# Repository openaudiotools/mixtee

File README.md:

# MIXTEE

**Open-source 16-input / 8-output digital mixer with MIDI control and 16-track recording.**

Built around the Teensy 4.1, MIXTEE is a compact desktop mixer designed for electronic musicians, synth enthusiasts, and DIY audio builders. It handles mixing, monitoring, MIDI control, multitrack recording to SD card, and 16-in/8-out AES67 network audio — all in a 260 × 100 × 50 mm enclosure.

## Features

- **16 mono inputs** (8 stereo pairs) with per-channel gain, pan, mute, solo
- **8 outputs** (master stereo + 3 aux/FX sends)
- **16-track recording** direct to SD card (48 kHz / 24-bit WAV, 8 MB PSRAM buffer)
- **DAW connectivity** (16-in / 8-out via AES67 over Ethernet)
- **MIDI control** via 2× USB host ports + TRS MIDI in/out
- **4.3" TFT display** with 3 dedicated encoders (NavX, NavY, Edit) and 16 illuminated CHOC keys
- **Compact form factor** — 260 × 100 × 50 mm, all controls on top, all audio on back

## Architecture

MIXTEE uses four AK4619VN codecs on two TDM buses, driven by the Teensy 4.1's Cortex-M7 at 600 MHz. The analog front-end features OPA1678 op-amps with Sallen-Key anti-alias and reconstruction filters. Power is supplied via USB-C (5V/5A USB PD, fallback 5V/3A). DAW connectivity uses AES67 network audio over Ethernet (100 Mbps, DP83825I PHY on Teensy).

## Repository Structure

```
mixtee/
├── README.md              ← you are here
├── LICENSE                ← MIT (firmware) + CERN-OHL-P v2 (hardware) + CC BY 4.0 (docs)
├── docs/                  ← system-level design specifications
│   ├── system-topology.md ← board summary, connector summary, back panel layout
│   ├── hardware.md        ← codecs, power system, BOM, target specs
│   ├── pin-mapping.md     ← Teensy 4.1 pin assignments, GPIO budget
│   ├── features.md        ← control interface, mixing, recording, MIDI, USB audio
│   ├── firmware.md        ← software architecture, libraries, state management
│   ├── ui-architecture.md ← view/page/module hierarchy, screen layouts
│   ├── enclosure.md       ← physical dimensions, panel layouts, jack spacing
│   ├── usb-audio.md       ← USB audio details + optional multitrack upgrade paths
│   ├── connector-parts.md ← connector MPN index
│   ├── pcb-design-rules.md ← trace widths, clearances, via sizes, manufacturing
│   └── pcbs-workflow.md   ← PCB design pipeline (SKiDL → FreeRouting → Gerbers)
├── hardware/              ← schematics, PCB, mechanical, BOM
│   ├── bom.csv            ← bill of materials
│   ├── mixtee-layout.*    ← panel layout (SVG, JPG, Affinity Designer)
│   ├── lib/               ← shared KiCad footprint library
│   └── pcbs/              ← per-board directories
│       ├── main/              ← Main Board (4-layer, not started)
│       ├── input-mother/      ← Input Mother Board (4-layer, routed)
│       ├── daughter-output/   ← Daughter/Output Board (2-layer, routed)
│       ├── io/                ← IO Board (2-layer, routed)
│       ├── key/               ← Key PCB (2-layer, routed)
│       └── power/             ← Power Board (off-the-shelf)
│       Each board has: README.md, connections.md, architecture.md,
│       CLAUDE.md, and designs/ (KiCad files + gerbers)
└── firmware/              ← Teensy 4.1 firmware (coming in Phase 1)
```

## Documentation

### System-Level Docs

| Document | Description |
| --- | --- |
| [System Topology](docs/system-topology.md) | Board summary, connector summary, back panel layout, mechanical mounting |
| [Hardware](docs/hardware.md) | Codec architecture, power system, BOM tables, target specs |
| [Pin Mapping](docs/pin-mapping.md) | Teensy 4.1 pin assignments, GPIO budget |
| [Features](docs/features.md) | Mixing, routing, recording, MIDI control, DAW audio |
| [Firmware](docs/firmware.md) | Software architecture, audio pipeline, state management |
| [UI Architecture](docs/ui-architecture.md) | Display hierarchy, navigation model, screen layouts |
| [Enclosure](docs/enclosure.md) | Physical dimensions, panel layouts, connector placement |
| [Network Connectivity](docs/network-connectivity.md) | AES67 network audio, DAW integration, discovery protocols |
| [Connector Parts](docs/connector-parts.md) | Connector MPN index |
| [PCB Design Rules](docs/pcb-design-rules.md) | Trace widths, clearances, via sizes, stackup, manufacturing rules |

### Per-Board Docs

Each board under `hardware/pcbs/` has its own `README.md` (concept), `connections.md` (pinouts), and `architecture.md` (circuits). See the [System Topology](docs/system-topology.md) for the board summary table with links.

## Status

**Pre-prototype / Design phase.** Hardware and firmware specifications are being finalized. Phase 1 breadboard bring-up is next.

## License

MIXTEE is fully open source. Hardware is licensed under CERN-OHL-P v2 (permissive), firmware under MIT, and documentation under CC BY 4.0. See [LICENSE](LICENSE) for details.

**Author:** Juliusz Fedyk — [openaudiotools.com](https://openaudiotools.com)

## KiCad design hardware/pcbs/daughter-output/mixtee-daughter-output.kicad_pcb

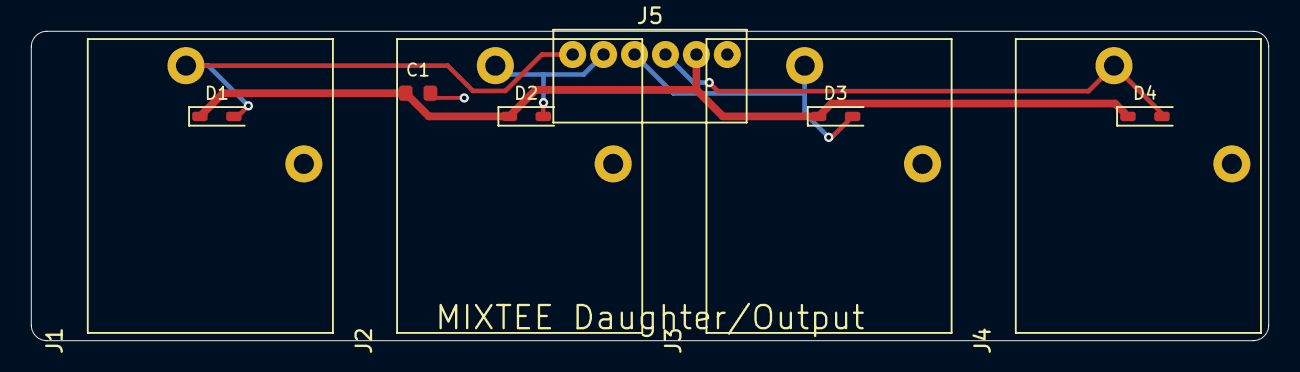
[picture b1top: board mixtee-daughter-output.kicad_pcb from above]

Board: 2 copper layers, 80.0 x 20.0 mm, 10 parts (0 on the bottom side), 6 nets.

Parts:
C1: 100nF; C_0603_1608Metric
D1, D2, D3, D4: BAT54; D_SOD-323
J1, J2, J3, J4: 112BPC; Switchcraft_112BPC
J5: B6B-PH-K-S; JST_PH_B6B-PH-K_1x06_P2.00mm_Vertical

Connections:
+5VA: C1.1, D1.1, D2.1, D3.1, D4.1, J5.5
AIN1: D1.2, J1.T, J5.1
AIN2: D2.2, J2.T, J5.2
AIN3: D3.2, J3.T, J5.3
AIN4: D4.2, J4.T, J5.4
GND: C1.2, J1.S, J2.S, J3.S, J4.S, J5.6

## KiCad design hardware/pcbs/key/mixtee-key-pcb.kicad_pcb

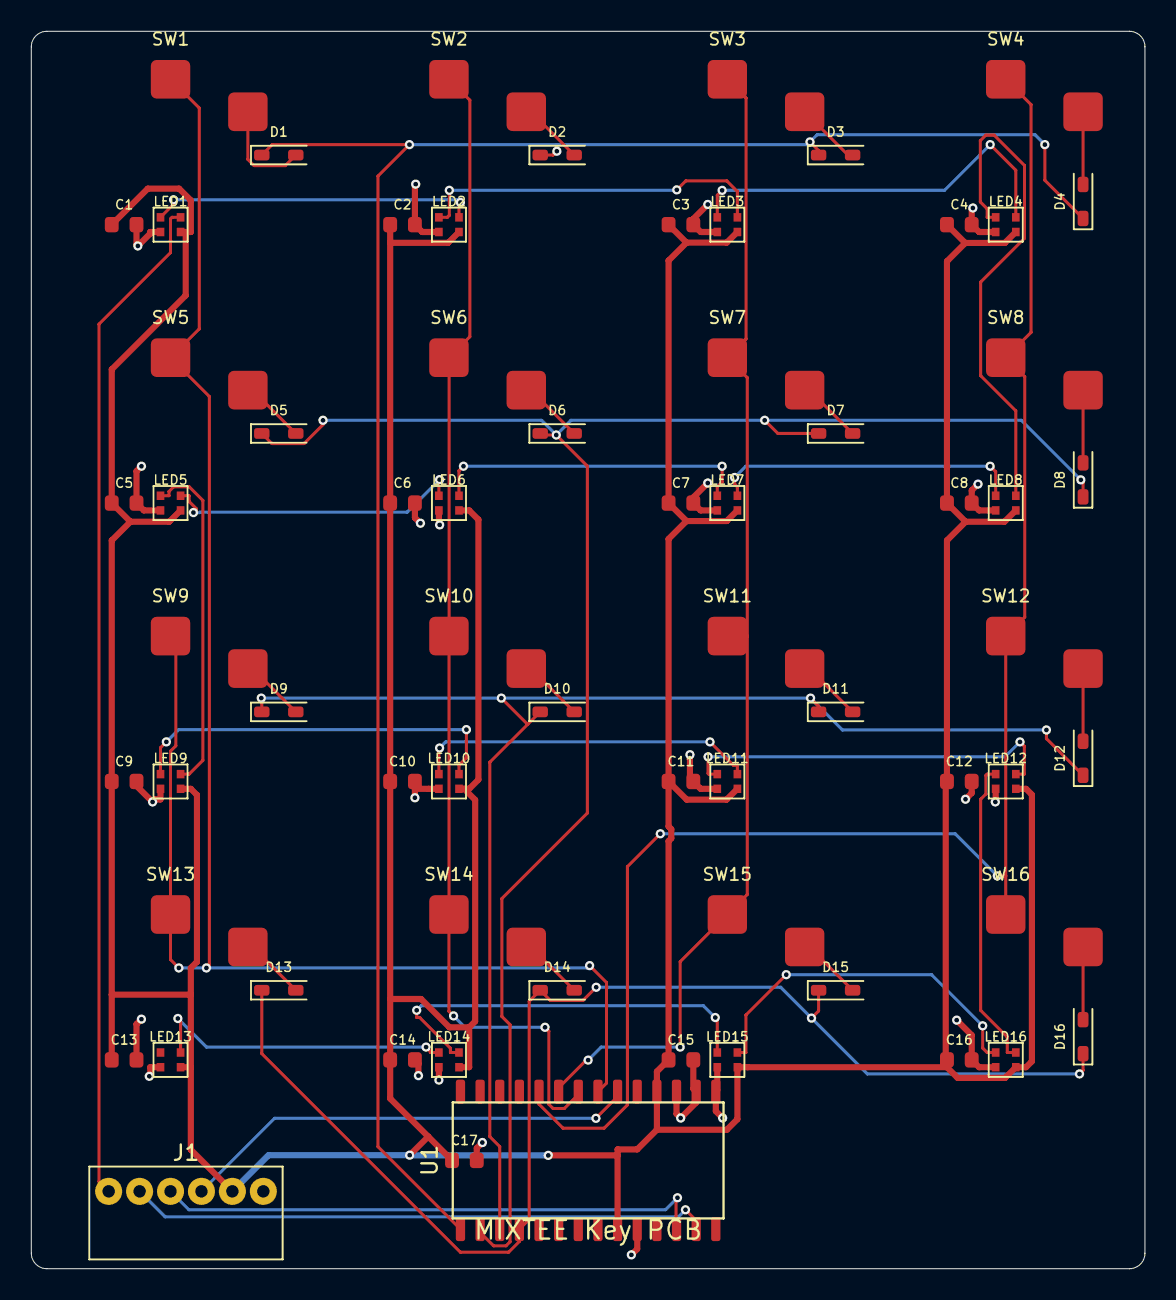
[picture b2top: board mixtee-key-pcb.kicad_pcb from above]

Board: 2 copper layers, 72.0 x 80.0 mm, 67 parts (0 on the bottom side), 45 nets.

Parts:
C1, C2, C3, C4, C5, C6, C7, C8, C9, C10, C11, C12, C13, C14, C15, C16, C17: 100nF; C_0603_1608Metric
D1, D2, D3, D4, D5, D6, D7, D8, D9, D10, D11, D12, D13, D14, D15, D16: 1N4148; D_SOD-123
J1: B6B-PH-K-S; JST_PH_B6B-PH-K_1x06_P2.00mm_Vertical
LED1, LED2, LED3, LED4, LED5, LED6, LED7, LED8, LED9, LED10, LED11, LED12, LED13, LED14, LED15, LED16: WS2812B-2020
SW1, SW2, SW3, SW4, SW5, SW6, SW7, SW8, SW9, SW10, SW11, SW12, SW13, SW14, SW15, SW16: CPG135001S30; Kailh_Choc_V1_Hotswap
U1: MCP23017; SOIC-28W_7.5x17.9mm_P1.27mm

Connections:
5V: C1.1, C2.1, C3.1, C4.1, C5.1, C6.1, C7.1, C8.1, C9.1, C10.1, C11.1, C12.1, C13.1, C14.1, C15.1, C16.1, C17.1, J1.5, LED1.3, LED2.3, LED3.3, LED4.3, LED5.3, LED6.3, LED7.3, LED8.3, LED9.3, LED10.3, LED11.3, LED12.3, LED13.3, LED14.3, LED15.3, LED16.3, U1.9, U1.18
COL0: SW1.1, SW5.1, SW9.1, SW13.1, U1.21
COL1: SW2.1, SW6.1, SW10.1, SW14.1, U1.22
COL2: SW3.1, SW7.1, SW11.1, SW15.1, U1.23
COL3: SW4.1, SW8.1, SW12.1, SW16.1, U1.24
GND: C1.2, C2.2, C3.2, C4.2, C5.2, C6.2, C7.2, C8.2, C9.2, C10.2, C11.2, C12.2, C13.2, C14.2, C15.2, C16.2, C17.2, J1.6, LED1.2, LED2.2, LED3.2, LED4.2, LED5.2, LED6.2, LED7.2, LED8.2, LED9.2, LED10.2, LED11.2, LED12.2, LED13.2, LED14.2, LED15.2, LED16.2, U1.10, U1.15, U1.16, U1.17
INT: J1.4, U1.20
NEO_D0: LED1.1, LED2.4
NEO_D1: LED2.1, LED3.4
NEO_D2: LED3.1, LED4.4
NEO_D3: LED4.1, LED8.4
NEO_D4: LED7.4, LED8.1
NEO_D5: LED6.4, LED7.1
NEO_D6: LED5.4, LED6.1
NEO_D7: LED5.1, LED9.4
NEO_D8: LED9.1, LED10.4
NEO_D9: LED10.1, LED11.4
NEO_D10: LED11.1, LED12.4
NEO_D11: LED12.1, LED16.4
NEO_D12: LED15.4, LED16.1
NEO_D13: LED14.4, LED15.1
NEO_D14: LED13.4, LED14.1
NEO_DIN: J1.1, LED1.4
ROW0: D1.1, D2.1, D3.1, D4.1, U1.1
ROW1: D5.1, D6.1, D7.1, D8.1, U1.2
ROW2: D9.1, D10.1, D11.1, D12.1, U1.3
ROW3: D13.1, D14.1, D15.1, D16.1, U1.4
SCL: J1.3, U1.12
SDA: J1.2, U1.13
SW1_D: D1.2, SW1.2
SW2_D: D2.2, SW2.2
SW3_D: D3.2, SW3.2
SW4_D: D4.2, SW4.2
SW5_D: D5.2, SW5.2
SW6_D: D6.2, SW6.2
SW7_D: D7.2, SW7.2
SW8_D: D8.2, SW8.2
SW9_D: D9.2, SW9.2
SW10_D: D10.2, SW10.2
SW11_D: D11.2, SW11.2
SW12_D: D12.2, SW12.2
SW13_D: D13.2, SW13.2
SW14_D: D14.2, SW14.2
SW15_D: D15.2, SW15.2
SW16_D: D16.2, SW16.2

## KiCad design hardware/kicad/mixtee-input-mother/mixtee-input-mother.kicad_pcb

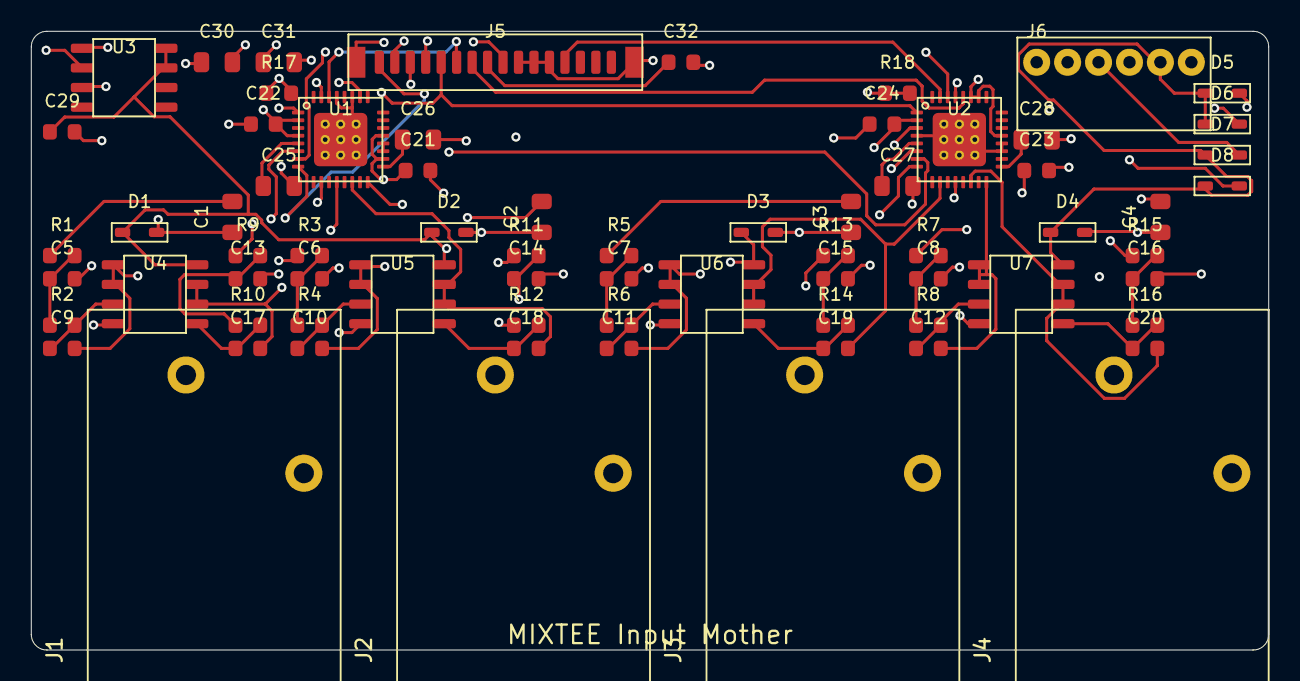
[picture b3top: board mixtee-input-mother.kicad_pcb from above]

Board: 4 copper layers, 80.0 x 40.0 mm, 71 parts (0 on the bottom side), 52 nets.

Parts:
C1, C2, C3, C4, C31: 10uF; C_0805_2012Metric
C5, C6, C7, C8, C13, C14, C15, C16: 6.8nF; C_0603_1608Metric
C9, C10, C11, C12, C17, C18, C19, C20: 3.3nF; C_0603_1608Metric
C21, C22, C23, C24, C29, C32: 100nF; C_0603_1608Metric
C25, C26, C27, C28: 2.2uF; C_0805_2012Metric
C30: 1uF; C_0805_2012Metric
D1, D2, D3, D4, D5, D6, D7, D8: ESD; D_SOD-323
J1, J2, J3, J4: 112BPC; Switchcraft_112BPC
J5: FFC-16; FFC_16pin_1mm
J6: B6B-PH-K-S; JST_PH_B6B-PH-K_1x06_P2.00mm_Vertical
R1, R2, R3, R4, R5, R6, R7, R8, R9, R10, R11, R12, R13, R14, R15, R16: 1k; R_0603_1608Metric
R17, R18: 10k; R_0603_1608Metric
U1, U2: AK4619VN; QFN-32-1EP_5x5mm_P0.5mm_EP3.45x3.45mm
U3: ADP7118; SOIC-8_3.9x4.9mm_P1.27mm
U4, U5, U6, U7: OPA1678; SOIC-8_3.9x4.9mm_P1.27mm

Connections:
5V_A: C29.1, D1.1, D2.1, D3.1, D4.1, D5.1, D6.1, D7.1, D8.1, J5.9, J6.5, U3.7, U3.8, U4.8, U5.8, U6.8, U7.8
5V_DIG: C32.1, J5.8
AIN_1_AC: C1.2, R1.1
AIN_3_AC: C2.2, R3.1
AIN_5_AC: C3.2, R5.1
AIN_7_AC: C4.2, R7.1
BCLK: J5.2, U1.7, U2.7
DAIN_R1: D5.2, J6.1, R9.1
DAIN_R2: D6.2, J6.2, R11.1
DAIN_R3: D7.2, J6.3, R13.1
DAIN_R4: D8.2, J6.4, R15.1
FILT_IN_1: C9.1, R2.2, U4.3
FILT_IN_3: C10.1, R4.2, U5.3
FILT_IN_5: C11.1, R6.2, U6.3
FILT_IN_7: C12.1, R8.2, U7.3
FILT_IN_R1: C17.1, R10.2, U4.5
FILT_IN_R2: C18.1, R12.2, U5.5
FILT_IN_R3: C19.1, R14.2, U6.5
FILT_IN_R4: C20.1, R16.2, U7.5
FN1_1: C5.1, R1.2, R2.1
FN1_3: C6.1, R3.2, R4.1
FN1_5: C7.1, R5.2, R6.1
FN1_7: C8.1, R7.2, R8.1
FN1_R1: C13.1, R9.2, R10.1
FN1_R2: C14.1, R11.2, R12.1
FN1_R3: C15.1, R13.2, R14.1
FN1_R4: C16.1, R15.2, R16.1
FOUT_1: C9.2, U1.12, U4.1, U4.2
FOUT_3: C10.2, U1.16, U5.1, U5.2
FOUT_5: C11.2, U2.12, U6.1, U6.2
FOUT_7: C12.2, U2.16, U7.1, U7.2
FOUT_R1: C17.2, U1.10, U4.6, U4.7
FOUT_R2: C19.2, U2.10, U6.6, U6.7
FOUT_R3: C20.2, U2.14, U7.6, U7.7
FOUT_R4: C18.2, U1.14, U5.6, U5.7
GND: C5.2, C6.2, C7.2, C8.2, C13.2, C14.2, C15.2, C16.2, C21.2, C22.2, C23.2, C24.2, C25.2, C26.2, C27.2, C28.2, C29.2, C30.2, C31.2, C32.2, J1.S, J2.S, J3.S, J4.S, J5.10, J5.11, J5.12, J5.MP, J6.6, U1.2, U1.4, U1.19, U1.20, U1.27, U1.29, U1.33, U2.2, U2.4, U2.19, U2.20, U2.29, U2.33, U3.3, U4.4, U5.4, U6.4, U7.4
JACK_1: C1.1, D1.2, J1.T
JACK_2: C2.1, D2.2, J2.T
JACK_3: C3.1, D3.2, J3.T
JACK_4: C4.1, D4.2, J4.T
LRCLK: J5.3, U1.6, U2.6
MCLK: J5.1, U1.8, U2.8
SCL: J5.7, U1.28, U2.28
SDA: J5.6, U1.30, U2.30
SDIN1: J5.5, U1.1, U2.1
SDOUT1: J5.4, U1.31
SDOUT2: J5.13, U2.31
U1_AVDRV: C25.1, U1.5
U1_VCOM: C26.1, U1.17
U2_AVDRV: C27.1, U2.5
U2_VCOM: C28.1, U2.17
V33_A: C21.1, C22.1, C23.1, C24.1, C30.1, C31.1, R17.1, R17.2, R18.1, R18.2, U1.3, U1.18, U1.21, U1.26, U2.3, U2.18, U2.21, U2.26, U2.27, U3.1, U3.2

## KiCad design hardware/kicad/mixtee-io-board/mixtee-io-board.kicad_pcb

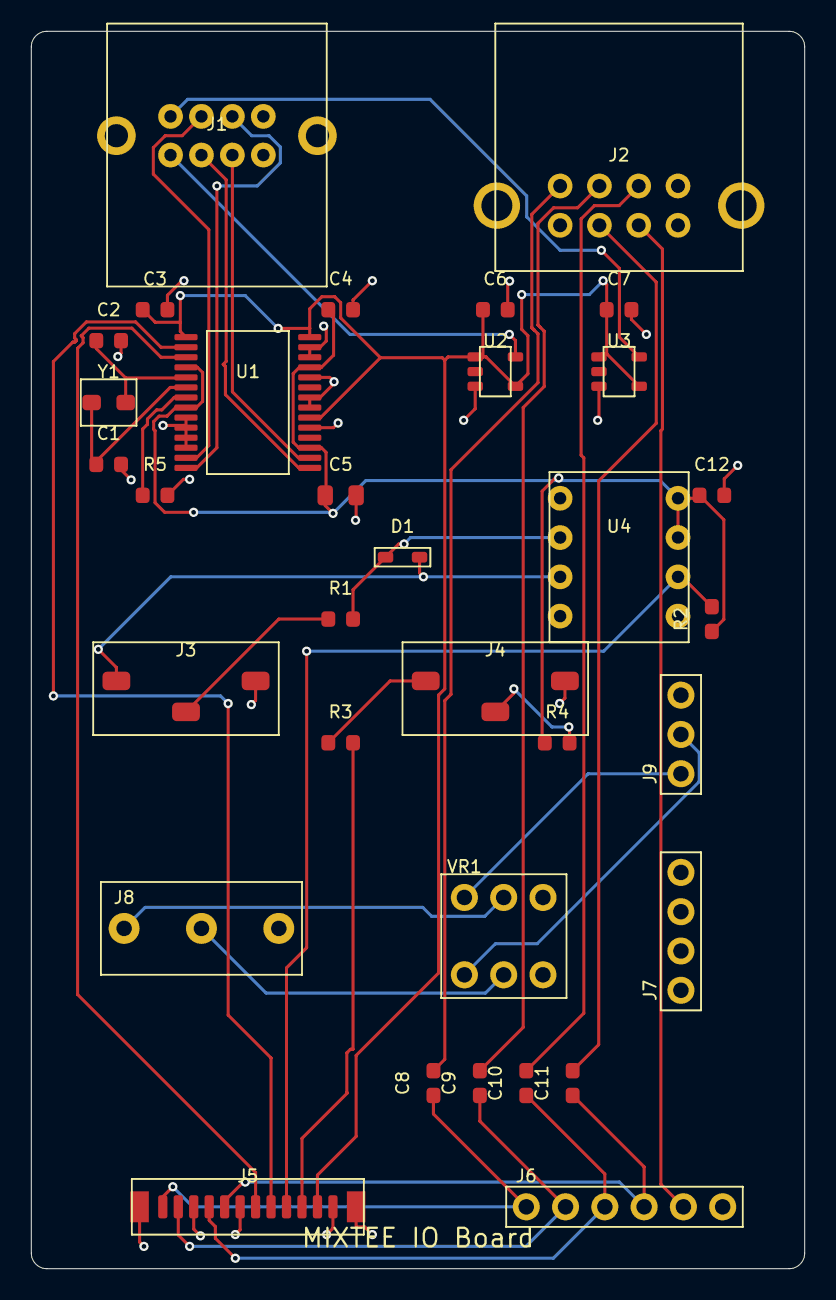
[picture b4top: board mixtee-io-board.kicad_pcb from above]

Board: 2 copper layers, 50.0 x 80.0 mm, 33 parts (0 on the bottom side), 34 nets.

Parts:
C1, C2: 15pF; C_0603_1608Metric
C3, C4, C6, C7, C8, C9, C10, C11, C12: 100nF; C_0603_1608Metric
C5: 10uF; C_0805_2012Metric
D1: 1N4148; D_SOD-123
J1: 67298-4090; USB_A_Amphenol_67298-4090_Dual
J2: RJ45_MagJack
J3, J4: SJ-3523-SMT; CUI_SJ-3523-SMT
J5: FFC-12; FFC_12pin_1mm
J6: ETH_HDR; PinHeader_1x06_P2.54mm_Vertical
J7: HP_BRK; PinHeader_1x04_P2.54mm_Vertical
J8: HP_TRS; Jack_3.5mm_Switchcraft_35RASMT2BHNTRX
J9: HP_OUT; PinHeader_1x03_P2.54mm_Vertical
R1: 220; R_0603_1608Metric
R2: 470; R_0603_1608Metric
R3: 33; R_0603_1608Metric
R4: 10; R_0603_1608Metric
R5: 12k; R_0603_1608Metric
U1: FE1.1s; SSOP-28_5.3x10.2mm_P0.65mm
U2, U3: TPS2051; SOT-23-5
U4: 6N138; DIP-8_W7.62mm
VR1: 10k_Dual; Potentiometer_Dual
Y1: 12MHz; Crystal_SMD_3225-2Pin_3.2x2.5mm

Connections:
5V_DIG: C3.1, C6.1, C7.1, J5.11, U1.1, U1.20, U1.28, U2.1, U2.4, U3.1, U3.4
ETH_LED: J2.7, J6.5
ETH_RXN: C11.1, J5.5, J6.4
ETH_RXN_MJ: C11.2, J2.6
ETH_RXP: C10.1, J5.4, J6.3
ETH_RXP_MJ: C10.2, J2.3
ETH_TXN: C9.1, J5.2, J6.2
ETH_TXN_MJ: C9.2, J2.2
ETH_TXP: C8.1, J5.1, J6.1
ETH_TXP_MJ: C8.2, J2.1
GND: C1.2, C2.2, C3.2, C4.2, C5.2, C6.2, C7.2, C12.2, J1.4, J1.8, J1.S1, J1.S2, J2.4, J2.5, J2.8, J2.S1, J2.S2, J3.S, J4.S, J5.3, J5.6, J5.12, J5.MP, J6.6, J7.4, J8.S, J9.3, R5.2, U1.9, U1.10, U1.11, U1.12, U1.19, U1.21, U1.22, U1.24, U1.26, U1.27, U2.3, U3.3, U4.5, VR1.A3, VR1.B3
HP_AMP_L: J9.1, VR1.A1
HP_AMP_R: J9.2, VR1.B1
HP_OUT_L: J8.T, VR1.A2
HP_OUT_R: J8.R, VR1.B2
MIDI_IN_OA: D1.1, R1.2, U4.2
MIDI_IN_OK: D1.2, J3.T, U4.3
MIDI_IN_R: J3.R, R1.1
MIDI_OUT_SINK: J4.T, R3.1
MIDI_OUT_SRC: J4.R, R4.2
MIDI_RX: J5.9, R2.2, U4.6
MIDI_TX: J5.10, R3.2
REXT_N: R5.1, U1.7
USB_DN1_DM: J1.2, U1.15
USB_DN1_DP: J1.3, U1.16
USB_DN2_DM: J1.6, U1.13
USB_DN2_DP: J1.7, U1.14
USB_UP_DM: J5.8, U1.2
USB_UP_DP: J5.7, U1.3
V33: C4.1, C5.1, C12.1, R2.1, R4.1, U1.4, U1.8, U1.17, U1.25, U4.7, U4.8
VBUS1: J1.1, U2.5
VBUS2: J1.5, U3.5
XTAL_IN: C1.1, U1.6, Y1.1
XTAL_OUT: C2.1, U1.5, Y1.2

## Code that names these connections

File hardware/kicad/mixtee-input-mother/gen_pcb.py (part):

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    6: "BCLK",
    7: "LRCLK",
    8: "SDIN1",         # Teensy -> both codecs
    9: "SDOUT1",        # U1 -> Teensy (FFC pin 4)
    10: "SDOUT2",       # U2 -> Teensy (FFC pin 13)
    # I2C
    11: "SDA",
    12: "SCL",
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    # ── U1: AK4619VN codec (QFN-32), I2C addr 0x10 (CAD=low) ──
    # Channels: ADC2L=ch1, ADC2R=ch2, ADC1L=ch3, ADC1R=ch4
    # Pin mapping from ak4619-wiring.md:
    #   Pin 1: SDIN1, Pin 2: SDIN2, Pin 3: TVDD, Pin 4: VSS2
    #   Pin 5: AVDRV, Pin 6: LRCK, Pin 7: BICK, Pin 8: MCLK
    #   Pin 9: AIN5R(open), Pin 10: AIN4R(ch2), Pin 11: AIN5L(open), Pin 12: AIN4L(ch1)
    #   Pin 13: AIN2R(open), Pin 14: AIN1R(ch4), Pin 15: AIN2L(open), Pin 16: AIN1L(ch3)
    #   Pin 17: VCOM, Pin 18: AVDD, Pin 19: VSS1, Pin 20: VREFL
    #   Pin 21: VREFH, Pin 22: AOUT1L, Pin 23: AOUT1R, Pin 24: AOUT2L
    #   Pin 25: AOUT2R, Pin 26: PDN, Pin 27: CAD, Pin 28: SCL
    #   Pin 29: SI, Pin 30: SDA, Pin 31: SDOUT1, Pin 32: SDOUT2
    #   Pin 33: EP (exposed pad)
    cn["U1"] = {
        "1": 8,       # SDIN1 -> TDM data in
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        "13": 0,      # AIN2R -> open
        "14": 57,     # AIN1R -> FOUT_R2 (ch 4 R from daughter, filtered)
        "15": 0,      # AIN2L -> open
        "16": 39,     # AIN1L -> FOUT_3 (ch 3 filtered, note: pin16=ADC1L=ch3 per wiring doc)
        "17": 14,     # VCOM -> U1_VCOM
        "18": 3,      # AVDD -> V33_A
        "19": 1,      # VSS1 -> GND
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        "28": 12,     # SCL
        "29": 1,      # SI -> VSS2 = GND (unused, I2C mode)
        "30": 11,     # SDA
        "31": 9,      # SDOUT1 -> SDOUT1 (FFC pin 4)
        "32": 0,      # SDOUT2 -> open (goes low in TDM)
        "33": 1,      # EP -> GND
    }
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        "13": 0,      # AIN2R -> open
        "14": 56,     # AIN1R -> FOUT_R4 (ch 8 R from daughter, filtered)
        "15": 0,      # AIN2L -> open
        "16": 43,     # AIN1L -> FOUT_7 (ch 7 filtered, note: pin16=ADC1L=ch7)
        "17": 16,     # VCOM -> U2_VCOM
        "18": 3,      # AVDD -> V33_A
        "19": 1,      # VSS1 -> GND
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        "28": 12,     # SCL
        "29": 1,      # SI -> VSS2 = GND
        "30": 11,     # SDA
        "31": 10,     # SDOUT1 -> SDOUT2 (FFC pin 13)
        "32": 0,      # SDOUT2 -> open
        "33": 1,      # EP -> GND
    }
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    # C2 connects from op-amp IN+ to op-amp OUT.

    # For the L channels (ch 1,3,5,7 on this board):
    # Ch 1: AIN_1_AC -[R1]-> FN1_1 -[R2]-> U4 pin3 (IN+_A)
    #        C_a: FN1_1 to GND; C_b: U4 pin3 to U4 pin1 (OUT_A = FOUT_1)
    # Ch 3: AIN_3_AC -[R3]-> FN1_3 -[R4]-> U5 pin3
    # Ch 5: AIN_5_AC -[R5]-> FN1_5 -[R6]-> U6 pin3
    # Ch 7: AIN_7_AC -[R7]-> FN1_7 -[R8]-> U7 pin3

    # For C_b: it connects op-amp IN+ to OUT. Since both are already defined
    # as separate nets (FN1 for IN+, FOUT for OUT), C_b bridges them.
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    # which is the same node where C2 connects. Let's call this the op-amp
    # input node = same as what we feed to op-amp IN+.

    # I already mapped op-amp IN+ (e.g. U4 pin3) to FN1_1. So FN1_1 IS
    # the op-amp IN+ node. Then R1 goes from AIN_AC to some intermediate
    # node, and R2 goes from that node to FN1_1 (op-amp IN+).
    # That intermediate node needs its own net. Let's reuse: the "between
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    cn["C32"] = {"1": 4, "2": 1}     # 5V_DIG local: 5V_DIG -> GND (100nF)

    # PDN pull-up resistors
    cn["R17"] = {"1": 3, "2": 3}     # V33_A to U1 PDN (both sides V33_A since PDN pin=V33_A)
    cn["R18"] = {"1": 3, "2": 3}     # V33_A to U2 PDN

    # Fix: update op-amp IN+ pins to use FILT_IN nets instead of FN1
    cn["U4"]["3"] = 58     # IN+_A -> FILT_IN_1
    cn["U4"]["5"] = 62     # IN+_B -> FILT_IN_R1
    cn["U5"]["3"] = 59     # IN+_A -> FILT_IN_3
    cn["U5"]["5"] = 63     # IN+_B -> FILT_IN_R2
    cn["U6"]["3"] = 60     # IN+_A -> FILT_IN_5
    cn["U6"]["5"] = 64     # IN+_B -> FILT_IN_R3
    cn["U7"]["3"] = 61     # IN+_A -> FILT_IN_7
    cn["U7"]["5"] = 65     # IN+_B -> FILT_IN_R4

    return cn

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
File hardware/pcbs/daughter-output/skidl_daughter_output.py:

"""
MIXTEE Daughter/Output Board - SKiDL Netlist Generator

Board: Universal Daughter/Output (80 x 20 mm, 2-layer)
Instances: 5 (2x input daughter, 2x output top, 1x output bottom)

Components:
  - 4x 1/4" TS jacks (Switchcraft 112BPC)
  - 4x BAT54 ESD clamp diodes (SOD-323)
  - 1x 100nF decoupling cap (0603)
  - 1x 6-pin JST-PH connector (B6B-PH-K-S) to mother board

Nets:
  - AIN1..AIN4: Analog signals (jack tip -> connector)
  - +5VA: Analog power from mother board
  - GND: Ground

ESD protection: BAT54 anode on signal, cathode on +5VA rail.
Decoupling cap: 100nF across +5VA and GND.
"""

import os

# Set KiCad symbol library path before importing skidl
os.environ["KICAD_SYMBOL_DIR"] = r"D:\programs\KiCad\9.0\share\kicad\symbols"

from skidl import *

# Manually add KiCad library path (SKiDL doesn't always pick up env vars)
lib_search_paths[KICAD].append(r"D:\programs\KiCad\9.0\share\kicad\symbols")

# ---------------------------------------------------------------------------
# Configuration
# ---------------------------------------------------------------------------

# Footprint references
CUSTOM_FP_LIB = "mixtee-footprints"
FP_112BPC = f"{CUSTOM_FP_LIB}:Switchcraft_112BPC"
FP_SOD323 = "Diode_SMD:D_SOD-323"
FP_C0603 = "Capacitor_SMD:C_0603_1608Metric"
FP_JST_PH_6 = "Connector_JST:JST_PH_B6B-PH-K_1x06_P2.00mm_Vertical"

NUM_CHANNELS = 4

# ---------------------------------------------------------------------------
# Named nets
# ---------------------------------------------------------------------------

gnd = Net("GND")
gnd.drive = POWER

vcc = Net("+5VA")
vcc.drive = POWER

ain = [Net(f"AIN{i+1}") for i in range(NUM_CHANNELS)]

# ---------------------------------------------------------------------------
# Components
# ---------------------------------------------------------------------------

# 4x 1/4" TS jacks (Switchcraft 112BPC)
# Connector_Audio:AudioJack2 pins: T (Tip=signal), S (Sleeve=ground)
jacks = []
for i in range(NUM_CHANNELS):
    j = Part(
        "Connector_Audio",
        "AudioJack2",
        footprint=FP_112BPC,
        ref=f"J{i+1}",
        value="112BPC",
    )
    j["T"] += ain[i]    # Tip carries the analog signal
    j["S"] += gnd        # Sleeve is ground
    jacks.append(j)

# 4x ESD protection diodes (Schottky, SOD-323)
# Device:D_Schottky pins: 1=K (Cathode), 2=A (Anode)
# ESD clamp: anode on signal, cathode on +5VA rail
diodes = []
for i in range(NUM_CHANNELS):
    d = Part(
        "Device",
        "D_Schottky",
        footprint=FP_SOD323,
        ref=f"D{i+1}",
        value="BAT54",
    )
    d["A"] += ain[i]    # Anode on signal
    d["K"] += vcc       # Cathode on +5VA supply
    diodes.append(d)

# 1x 100nF decoupling capacitor (0603)
# Device:C pins: 1, 2 (both passive)
cap = Part(
    "Device",
    "C",
    footprint=FP_C0603,
    ref="C1",
    value="100nF",
)
cap[1] += vcc
cap[2] += gnd

# 1x 6-pin JST-PH connector to mother board (B6B-PH-K-S)
# Connector_Generic:Conn_01x06 pins: 1..6
# Pin assignment per docs/pcb-architecture.md (Mother <-> Daughter):
#   Pin 1: AIN1
#   Pin 2: AIN2
#   Pin 3: AIN3
#   Pin 4: AIN4
#   Pin 5: +5VA
#   Pin 6: GND
conn = Part(
    "Connector_Generic",
    "Conn_01x06",
    footprint=FP_JST_PH_6,
    ref="J5",
    value="B6B-PH-K-S",
)
for i in range(NUM_CHANNELS):
    conn[i + 1] += ain[i]
conn[5] += vcc
conn[6] += gnd

# ---------------------------------------------------------------------------
# ERC and netlist generation
# ---------------------------------------------------------------------------

if __name__ == "__main__":
    ERC()
    generate_netlist()
    print(f"\nDaughter/Output board netlist generated successfully.")
    print(f"Components: {NUM_CHANNELS} jacks + {NUM_CHANNELS} diodes + 1 cap + 1 connector = {2*NUM_CHANNELS + 2} total")
